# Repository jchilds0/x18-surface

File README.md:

# x18-surface
Control Surface for Behringer X18

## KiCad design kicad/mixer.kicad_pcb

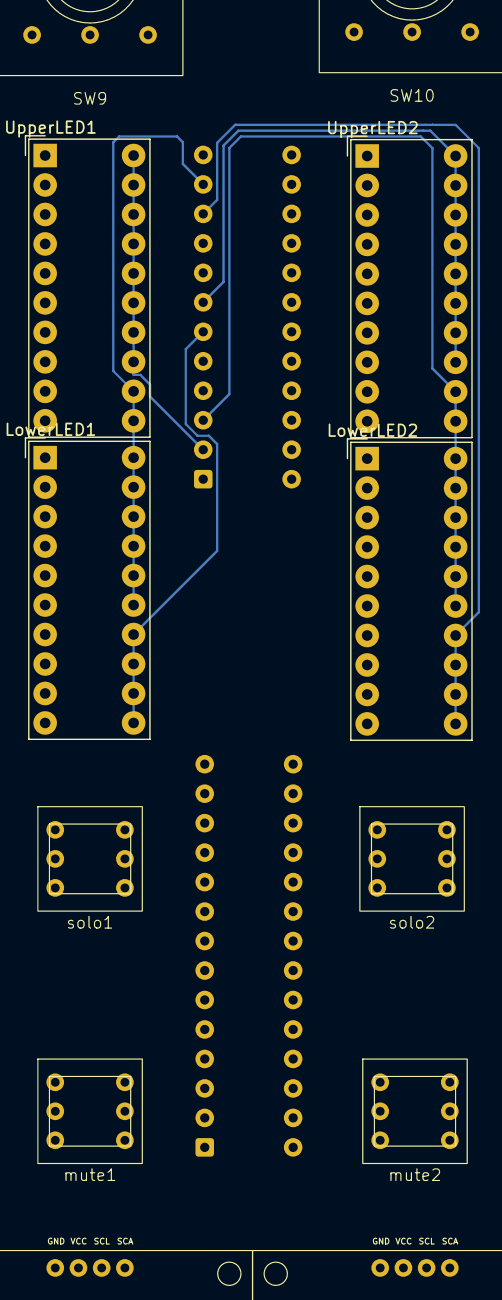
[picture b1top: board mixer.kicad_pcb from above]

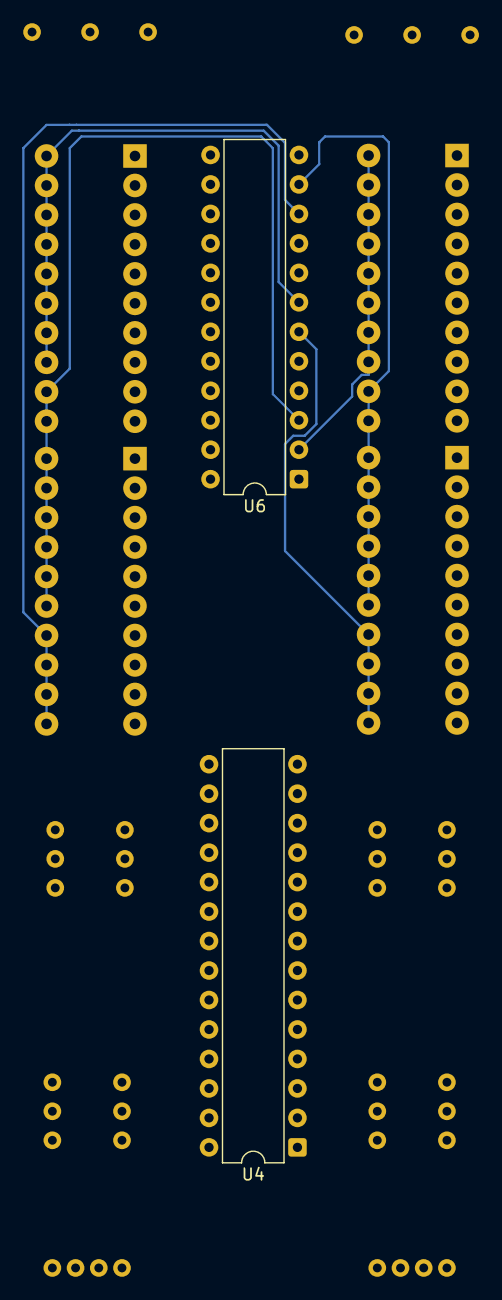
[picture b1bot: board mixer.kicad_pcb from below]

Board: 4 copper layers, 14 parts (2 on the bottom side), 28 nets.

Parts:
LowerLED1, LowerLED2: HDSP-4832_2; HDSP-4832
SW9, SW10: RotaryEncoder
U4: MCP23017_SP; DIP-28_W7.62mm
U6: MAX7219; DIP-24_W7.62mm
UpperLED1, UpperLED2: HDSP-4832_2; HDSP-4832
mute1, mute2: SW_SPST_LED; SW_SPST_LED_9mm
oled1, oled2: oled
solo1, solo2: SW_SPST_LED; SW_SPST_LED_9mm

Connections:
+5V: SW9.3 (C), SW10.3 (C), U4.9 (VDD), U6.19 (V+), mute1.1, mute2.1, oled1.2 (VCC), oled2.2 (VCC), solo1.1, solo2.1
Earth: U4.10 (VSS), U6.4 (GND), U6.9 (GND)
GND: oled1.1 (GND), oled2.1 (GND)
unnamed: SW9.1 (A), U4.7 (GPB6)
unnamed: SW9.2 (B), U4.8 (GPB7)
unnamed: SW10.1 (A), U4.21 (GPA0)
unnamed: SW10.2 (B), U4.22 (GPA1)
unnamed: U4.1 (GPB0), U6.13 (CLK)
unnamed: U4.2 (GPB1), U6.1 (DIN)
unnamed: U4.3 (GPB2), mute1.2
unnamed: U4.4 (GPB3), mute2.2
unnamed: U4.5 (GPB4), solo1.2
unnamed: U4.6 (GPB5), solo2.2
unnamed: U6.2 (DIG_0), UpperLED1.13 (K), UpperLED1.14 (K), UpperLED1.15 (K), UpperLED1.16 (K), UpperLED1.17 (K), UpperLED1.18 (K), UpperLED1.19 (K), UpperLED1.20 (K)
unnamed: LowerLED1.15 (K), LowerLED1.16 (K), LowerLED1.17 (K), LowerLED1.18 (K), LowerLED1.19 (K), LowerLED1.20 (K), U6.11 (DIG_1), UpperLED1.11 (K), UpperLED1.12 (K)
unnamed: LowerLED1.11 (K), LowerLED1.12 (K), LowerLED1.13 (K), LowerLED1.14 (K), U6.6 (DIG_2)
unnamed: U6.7 (DIG_3), UpperLED2.13 (K), UpperLED2.14 (K), UpperLED2.15 (K), UpperLED2.16 (K), UpperLED2.17 (K), UpperLED2.18 (K), UpperLED2.19 (K), UpperLED2.20 (K)
unnamed: LowerLED2.15 (K), LowerLED2.16 (K), LowerLED2.17 (K), LowerLED2.18 (K), LowerLED2.19 (K), LowerLED2.20 (K), U6.3 (DIG_4), UpperLED2.11 (K), UpperLED2.12 (K)
unnamed: LowerLED2.11 (K), LowerLED2.12 (K), LowerLED2.13 (K), LowerLED2.14 (K), U6.10 (DIG_5)
unnamed: U6.5 (DIG_6), mute1.3 (K), mute2.3 (K), solo1.3 (K), solo2.3 (K)
unnamed: LowerLED1.7 (A), LowerLED2.7 (A), U6.14 (SEG_A), UpperLED1.1 (A), UpperLED1.9 (A), UpperLED2.1 (A), UpperLED2.9 (A), mute1.4 (A)
unnamed: LowerLED1.8 (A), LowerLED2.8 (A), U6.16 (SEG_B), UpperLED1.2 (A), UpperLED1.10 (A), UpperLED2.2 (A), UpperLED2.10 (A), solo1.4 (A)
unnamed: LowerLED1.1 (A), LowerLED1.9 (A), LowerLED2.1 (A), LowerLED2.9 (A), U6.20 (SEG_C), UpperLED1.3 (A), UpperLED2.3 (A), mute2.4 (A)
unnamed: LowerLED1.2 (A), LowerLED1.10 (A), LowerLED2.2 (A), LowerLED2.10 (A), U6.23 (SEG_D), UpperLED1.4 (A), UpperLED2.4 (A), solo2.4 (A)
unnamed: LowerLED1.6 (A), LowerLED2.6 (A), U6.22 (SEG_DP), UpperLED1.8 (A), UpperLED2.8 (A)
unnamed: LowerLED1.3 (A), LowerLED2.3 (A), U6.21 (SEG_E), UpperLED1.5 (A), UpperLED2.5 (A)
unnamed: LowerLED1.4 (A), LowerLED2.4 (A), U6.15 (SEG_F), UpperLED1.6 (A), UpperLED2.6 (A)
unnamed: LowerLED1.5 (A), LowerLED2.5 (A), U6.17 (SEG_G), UpperLED1.7 (A), UpperLED2.7 (A)

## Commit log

2024-07-16 slider files
2024-07-19 single channel logic
2024-07-21 gain, meter and display sheets
2024-07-21 input cleaning
2024-07-22 fader set
2024-07-23 kicad updates
2024-07-24 pcb routing 1
2024-07-27 pcb routing 2
2024-12-25 kicad - pcb routing
2026-03-10 update gitignore
2026-03-10 esp idf testing
2026-03-12 i2c basic setup
2026-03-13 mcp23017 button reading
2026-03-13 mcp23017 circuit update
2026-03-16 event loop max7219
2026-03-16 mcp23017 event loop
2026-03-18 fix timeouts
2026-03-18 event loop updates
2026-03-18 led update
2026-03-18 fix max7219 init
2026-03-18 mcp23017 interrupts
